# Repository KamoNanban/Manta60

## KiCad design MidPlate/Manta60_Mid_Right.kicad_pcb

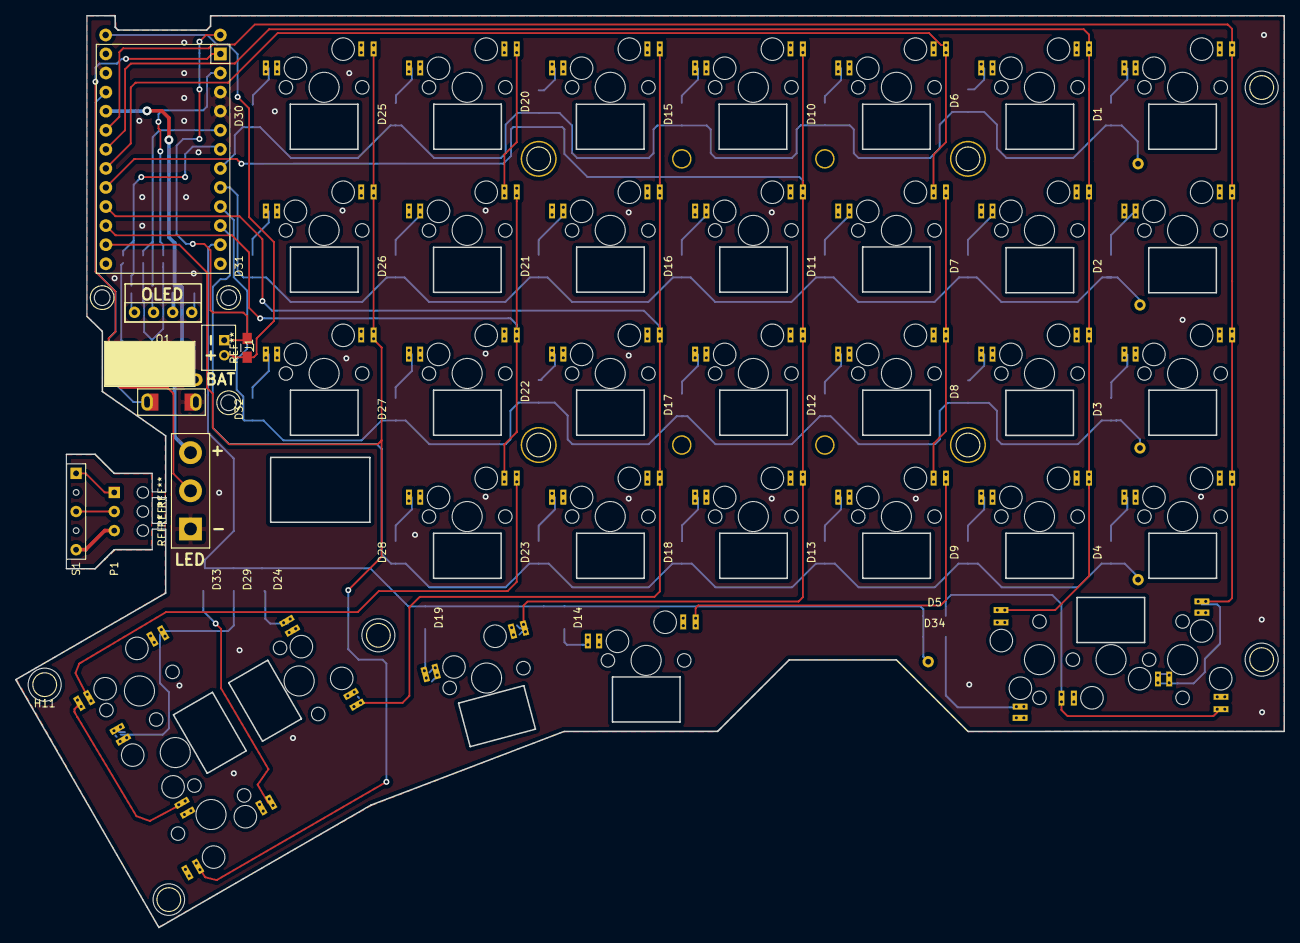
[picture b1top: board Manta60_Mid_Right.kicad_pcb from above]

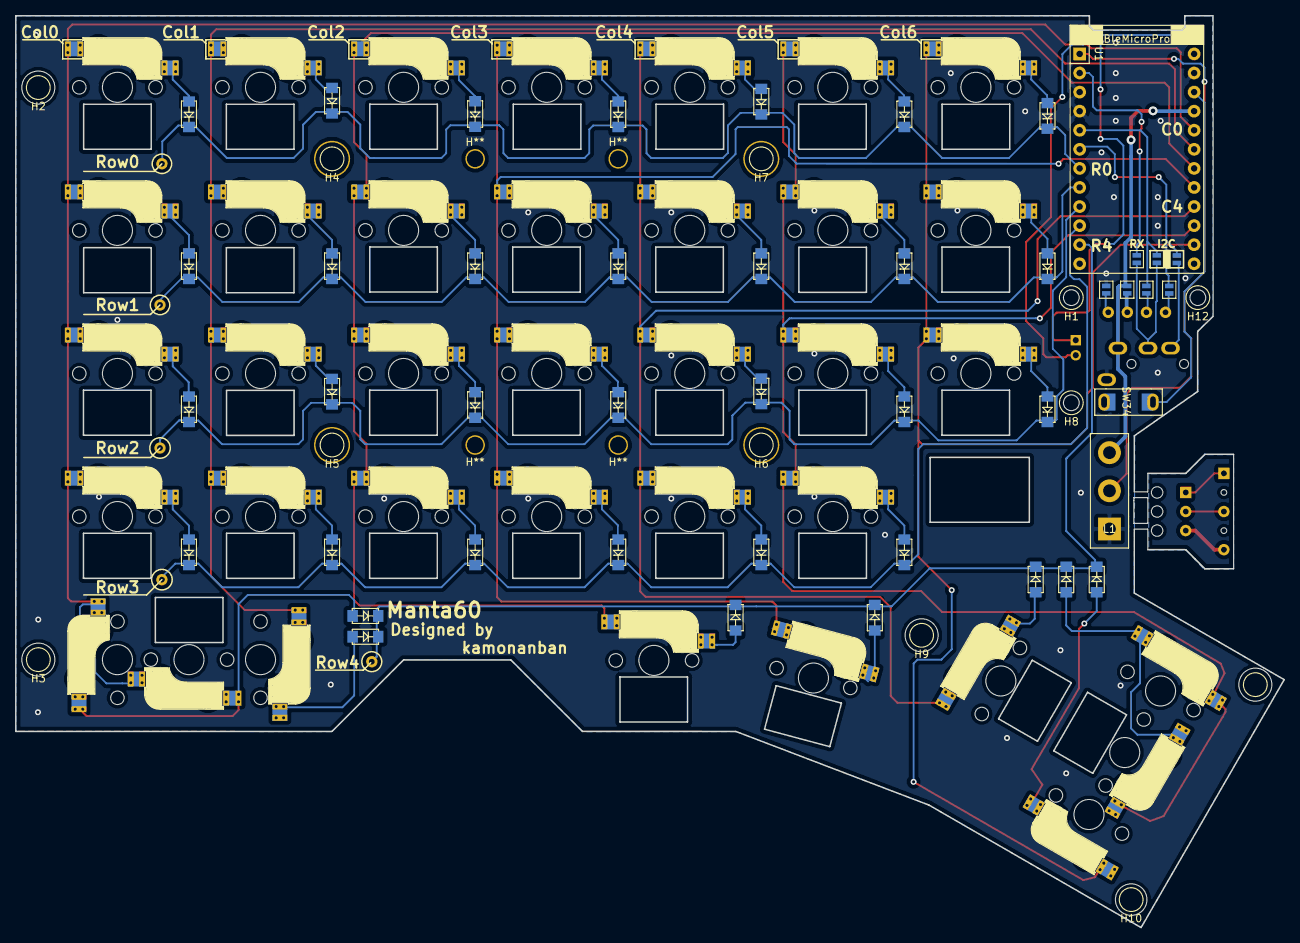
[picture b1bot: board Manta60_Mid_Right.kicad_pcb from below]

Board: 2 copper layers, 168.9 x 121.4 mm, 101 parts (25 on the bottom side), 64 nets.

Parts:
D1, D2, D3, D4, D5, D6, D7, D8, D9, D10, D11, D12, D13, D14, D15, D16, D17, D18, D19, D20, D21, D22, D23, D24, D25, D26, D27, D28, D29, D30, D31, D32, D33, D34: D; 1N4148_v01
H1, H2, H3, H9, H10, H11, H12: HOLE; M3
H4, H5, H6, H7: HOLE; M2_SP
H8: M3
H**: HOLE
H**#2, H**#3, H**#4: HOLE
J1: Conn_01x02; PH_2Pin_Top
JP1, JP2, JP3, JP4, JP5, JP6, JP7: Jumper3
L1: LED; LED-PIN
O1: OLED
P1: LED-pin; Led-pin
S1: LED-socket
SW1, SW2, SW3, SW4, SW6, SW7, SW8, SW9, SW10, SW11, SW12, SW13, SW14, SW15, SW16, SW17, SW18, SW19, SW20, SW21, SW22, SW23, SW24, SW25, SW26, SW27, SW28, SW30, SW31, SW32, SW33, SW35: SW_Push; CherryMX_Hotswap_right
SW5, SW5#2, SW29, SW29#2: SW_Push; CherryMX_Hotswap_left
SW34: Reset_SW; RST_SW
T1: TRRS; MJ-4PP-9_rev1
U1: ProMicro

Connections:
BAT: J1.1, U1.25
BAT_GND: J1.2, U1.26
Col0: SW1.1, SW2.1, SW3.1, SW4.1, SW5.1, SW5#2.1, U1.20
Col1: SW6.1, SW7.1, SW8.1, SW9.1, SW35.1, U1.19
Col2: SW10.1, SW11.1, SW12.1, SW13.1, SW14.1, U1.18
Col3: SW15.1, SW16.1, SW17.1, SW18.1, SW19.1, U1.17
Col4: SW20.1, SW21.1, SW22.1, SW23.1, SW24.1, U1.16
Col5: SW25.1, SW26.1, SW27.1, SW28.1, SW29.1, SW29#2.1, U1.15
Col6: SW30.1, SW31.1, SW32.1, SW33.1, U1.14
Data: JP7.2, U1.2
GND: JP1.2, L1.3, SW34.2, T1.A, U1.3, U1.4, U1.23
LED: L1.2, U1.1
unnamed: D1.2, SW1.2
unnamed: D2.2, SW2.2
unnamed: D3.2, SW3.2
unnamed: D4.2, SW4.2
unnamed: D5.2, SW5.2, SW5#2.2
unnamed: D6.2, SW6.2
unnamed: D7.2, SW7.2
unnamed: D8.2, SW8.2
unnamed: D9.2, SW9.2
unnamed: D10.2, SW10.2
unnamed: D11.2, SW11.2
unnamed: D12.2, SW12.2
unnamed: D13.2, SW13.2
unnamed: D14.2, SW14.2
unnamed: D15.2, SW15.2
unnamed: D16.2, SW16.2
unnamed: D17.2, SW17.2
unnamed: D18.2, SW18.2
unnamed: D19.2, SW19.2
unnamed: D20.2, SW20.2
unnamed: D21.2, SW21.2
unnamed: D22.2, SW22.2
unnamed: D23.2, SW23.2
unnamed: D24.2, SW24.2
unnamed: D25.2, SW25.2
unnamed: D26.2, SW26.2
unnamed: D27.2, SW27.2
unnamed: D28.2, SW28.2
unnamed: D29.2, SW29.2, SW29#2.2
unnamed: D30.2, SW30.2
unnamed: D31.2, SW31.2
unnamed: D32.2, SW32.2
unnamed: D33.2, SW33.2
unnamed: D34.2, SW35.2
unnamed: JP1.1, O1.1
unnamed: JP2.1, O1.2
unnamed: JP3.1, O1.3
unnamed: JP4.1, O1.4
unnamed: JP5.1, JP7.1, T1.C
unnamed: JP6.1, T1.B
unnamed: P1.1, S1.1
unnamed: P1.2, S1.2
unnamed: P1.3, S1.3
RST: SW34.1, U1.22
Row0: D1.1, D6.1, D10.1, D15.1, D20.1, D25.1, D30.1, U1.7
Row1: D2.1, D7.1, D11.1, D16.1, D21.1, D26.1, D31.1, U1.8
Row2: D3.1, D8.1, D12.1, D17.1, D22.1, D27.1, D32.1, U1.9
Row3: D4.1, D9.1, D13.1, D18.1, D23.1, D28.1, U1.10
Row4: D5.1, D14.1, D19.1, D24.1, D29.1, D33.1, D34.1, U1.11
SCL: JP3.2, JP5.2, U1.5
SDA: JP4.2, JP6.2, U1.6
VCC: JP2.2, L1.1, T1.D, U1.21

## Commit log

2018-12-18 Create EDLC_Chager
2019-01-26 rev0.1
    My first commit
2019-01-29 Create Manta60-BLE_PartsLayout_v01.pdf
    Manta60-BLE_PartsLayout_v01 Upload
2019-01-29 LayoutUp
    LayoutUPdate
2019-01-31 SVGData
    SVGFileUpload
2019-03-12 FootPrintUpdate
2019-04-17 rev1.h debug
2020-01-06 buildguide_update
2020-01-06 photo_upload
2020-01-18 rename
2020-01-19 photo_up
2020-01-19 photo_update
